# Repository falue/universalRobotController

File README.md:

# Universal Robot Control (RX/TX)

## Introduction

This repository includes transmitter (TX) and receiver (RX) arduino files for a remote controlled robot of any form.

The transmitter is a custom build to have full control over input mixing, skewing and do all sorts of dependencies.
It depends on a custom PCB, or like a thousand wires.
The receiver end can be a robot or whatever.

This relies on OrangeRx products by hobbyking for Tx/Rx and uses the (legacy) DSM2/DSMX† protocols for a reliable, digital communication.
with a "range of up to 3km (line of sight)".
I'm sure though this works with any RC transmitter that uses iBUs / ppm.

> Based on James Brutons RemoteDSM:
> 
> [https://github.com/XRobots/RemoteDSM ↗](https://github.com/XRobots/RemoteDSM)
> 
> [https://youtu.be/5BfRg9CUMYI ↗](https://youtu.be/5BfRg9CUMYI)

† "*The DSM in DSMX stands for Digital Spectrum Modulation and is what creates pure digital control providing an impenetrable radio link immune to all types of interference.*" ([Soruce ↗](https://www.spektrumrc.com/spm-bs-dsmx.html#:~:text=The%20DSM%20in%20DSMX%20stands,to%20all%20types%20of%20interference.))

# Transmission speed
Depending if you need 10 or 20 channels you can choose to use a second transmitter.
The second transmitter leads to more fluctation and/or longer duration of the main `loop()` though. If you need snappy response times, reconsider using a second transmitter.

|Num of Transmitters|Range (ms)|Average (ms)|Median (ms)|
|--|--|--|--|
|1|30-69|31|32|
|2|28-70|45|33|

# Hardware
## TX
- [Arduino Mega ↗](https://store.arduino.cc/products/arduino-mega-2560-rev3)
- One thousand switches and buttons
- One thousand linear potentiometers
- Two three-axis joysticks (ali express article [1↗](https://de.aliexpress.com/item/4001270851701.html) or [2↗](https://de.aliexpress.com/item/1005002965907648.html)) with a pushbutton
- A custom PCB (files here: [gerber.zip](kicad/universalRobotTx/gerber/gerber.zip) | [kicad](kicad/universalRobotTx))
- A laser cut case (files here: [ai](cad/universal_robot_laser.ai) | [dxf](cad/universal_robot_laser.dxf) | [svg](cad/universal_robot_laser.svg))
- One (or two) [OrangeRX DSMX DSM2 transmitter ↗](https://hobbyking.com/en_us/orangerx-dsmx-dsm2-compatible-2-4ghz-transmitter-module-v1-2.html)
- *..extensive list has to follow*

## RX
- [Arduino Leonardo (or UNO) ↗](https://store.arduino.cc/products/arduino-leonardo-with-headers)
- [Arduino Motor Shield Rev3 ↗](https://store.arduino.cc/products/arduino-motor-shield-rev3)
- One  (or two) [OrangeRx RR12RDTS Receiver ↗](https://hobbyking.com/en_us/orangerx-rr12rdts-receiver-with-s-link-dsm2-dsmx-compatible.html)
- [OrangeRx Program box ↗](https://hobbyking.com/en_us/orangerx-program-box-for-r620x-r1220x-v3-rr12rdts-receivers.html)
- *..extensive list has to follow*

---

# OrangeRx setup

## OrangeRx Receiver re-programming
As the Windows software "[rx_secure_configurator ↗](https://cdn-global-hk.hobbyking.com/media/file/r/x/rx_secure_configurator.zip?_gl=1*g1ywqd*_ga*MTM1ODE1NzExLjE3MTE0MDI5MjU.*_ga_5W5MJE4N6Q*MTcxNDIxNzU1Ni4xMS4xLjE3MTQyMTc2MTguNTkuMC4w)" for the [receiver ↗](https://hobbyking.com/en_us/orangerx-rr12rdts-receiver-with-s-link-dsm2-dsmx-compatible.html) to set some settings on the receiver is **very** buggy, buy the [OrangeRx Program box ↗](https://hobbyking.com/en_us/orangerx-program-box-for-r620x-r1220x-v3-rr12rdts-receivers.html).
1. Connect the jumper to power the receiver from the program box to pin 1 and 2.
2. Set the "out type" from default "*SBus*" to "*iBUS*"
3. Set the *FailSafe" to send "1500" on all channels when losing connection; to be able to detect signal loss on the receiver

## OrangeRx Binding Process
1. Power off remote.
2. Power on robot receiver. Its LED flashes fast yellow to indicate that there is no connection.
2. Press "Bind" button on transmitter.
3. Power on remote (!); keep "Bind" button pressed.
4. remote beeps three times; robot receiver stops flashing and has now a continous light. congrats.
5. From here on out, connection is established.

> 📝 NOTE: Red LED on remote (on the transmitter) does not turn on if no signal is sent to the PPM pin.
> 
> 📝 NOTE: Always power on robot receiver first, then remote.
> 
> 📝 NOTE: If turned off remote while robot receiver is on, restart robot receiver as well to reset connection.
> Turning off robot receiver while remote is still on, restarting robot receiver again auto connects again.

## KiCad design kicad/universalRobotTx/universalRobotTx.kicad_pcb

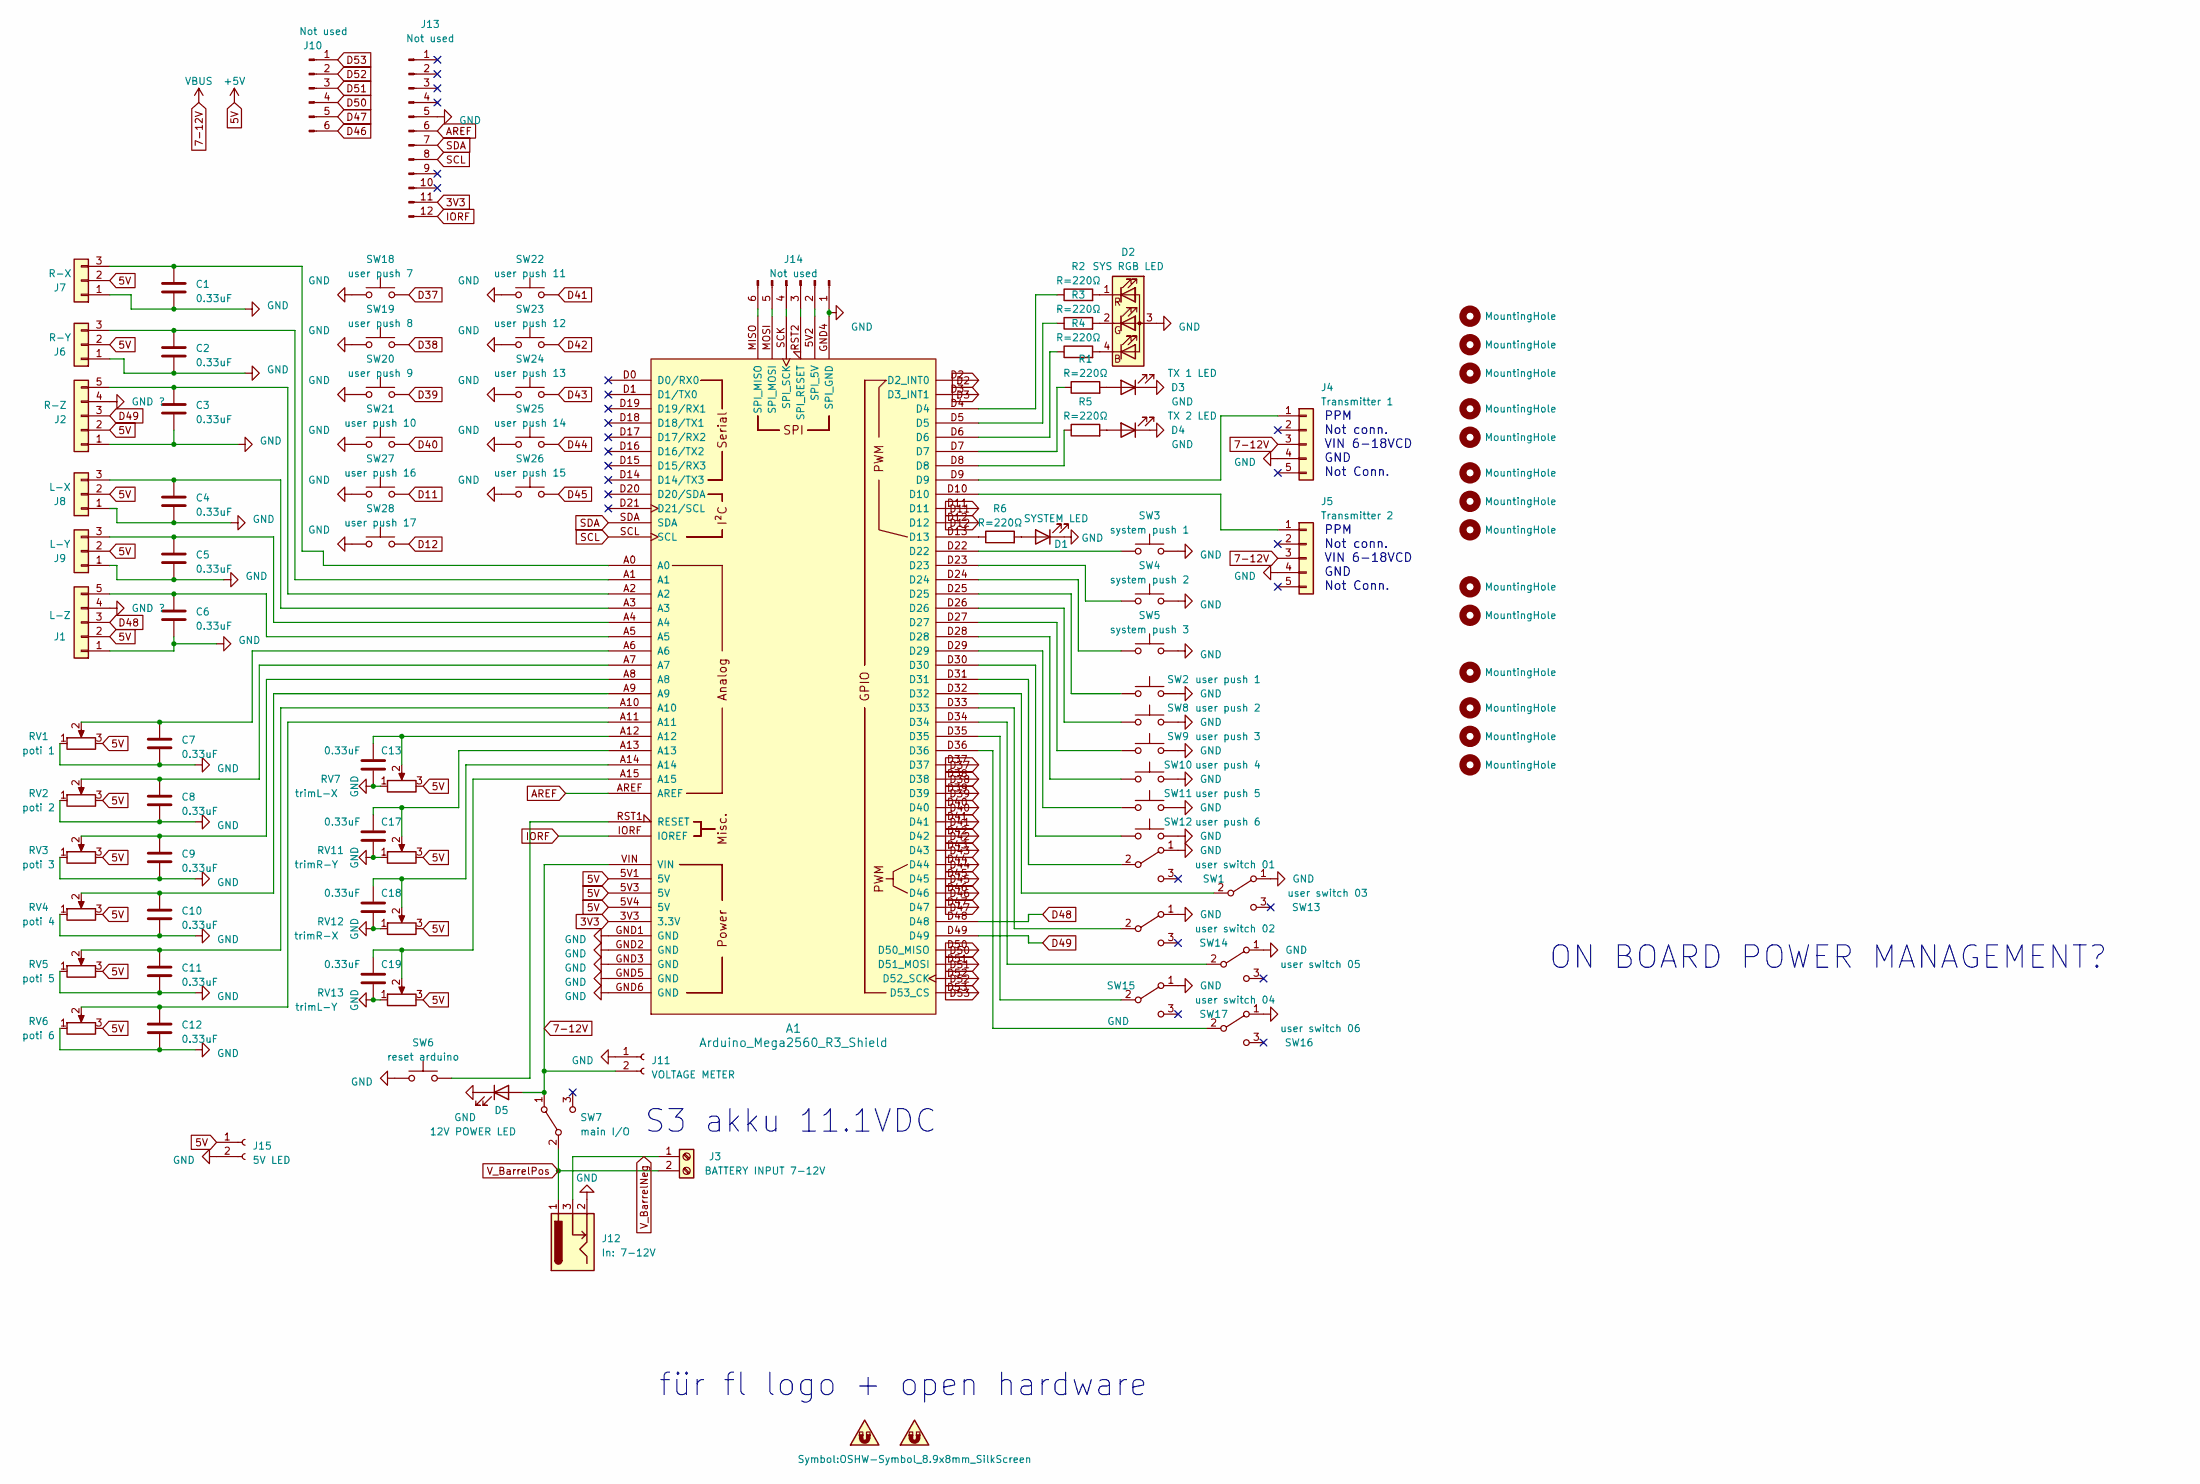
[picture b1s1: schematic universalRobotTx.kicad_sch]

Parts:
A1: Arduino_Mega2560_R3_Shield
C1, C2, C3, C4, C5, C6, C7, C8, C9, C10, C11, C12, C13, C17, C18, C19: 0.33uF; C_Disc_D7.0mm_W2.5mm_P5.00mm
D1: SYSTEM LED; LED_D3.0mm
D2: SYS RGB LED; LED_D5.0mm-4_RGB_Wide_Pins
D3: TX 1 LED; LED_D3.0mm
D4: TX 2 LED; LED_D3.0mm
D5: 12V POWER LED; LED_D3.0mm
H7: MountingHole; MountingHole_3mm
J1: L-Z; JST_PH_B5B-PH-K_1x05_P2.00mm_Vertical
J2: R-Z; JST_PH_B5B-PH-K_1x05_P2.00mm_Vertical
J3: BATTERY INPUT 7-12V; TerminalBlock_Phoenix_MKDS-1,5-2-5.08_1x02_P5.08mm_Horizont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
J4: Transmitter 1; JST_PH_B5B-PH-K_1x05_P2.00mm_Vertical
J5: Transmitter 2; JST_PH_B5B-PH-K_1x05_P2.00mm_Vertical
J6: R-Y; JST_PH_B3B-PH-K_1x03_P2.00mm_Vertical
J7: R-X; JST_PH_B3B-PH-K_1x03_P2.00mm_Vertical
J8: L-X; JST_PH_B3B-PH-K_1x03_P2.00mm_Vertical
J9: L-Y; JST_PH_B3B-PH-K_1x03_P2.00mm_Vertical
J10, J14: Not used; PinHeader_1x06_P2.54mm_Vertical
J11: VOLTAGE METER; JST_EH_B2B-EH-A_1x02_P2.50mm_Vertical
J12: In: 7-12V; BarrelJack_Kycon_KLDX-0202-xC_Horizontal
J13: Not used; PinHeader_1x12_P2.54mm_Vertical
J15: 5V LED; JST_EH_B2B-EH-A_1x02_P2.50mm_Vertical
R1, R2, R3, R4, R5, R6: R=220Ω; R_Axial_DIN0309_L9.0mm_D3.2mm_P5.08mm_Vertical
RV1: poti 1; Potentiometer_Bourns_PTV09A-1_Single_Vertical
RV2: poti 2; Potentiometer_Bourns_PTV09A-1_Single_Vertical
RV3: poti 3; Potentiometer_Bourns_PTV09A-1_Single_Vertical
RV4: poti 4; Potentiometer_Bourns_PTV09A-1_Single_Vertical
RV5: poti 5; Potentiometer_Bourns_PTV09A-1_Single_Vertical
RV6: poti 6; Potentiometer_Bourns_PTV09A-1_Single_Vertical
RV7: trimL-X; Potentiometer_Bourns_3386X_Horizontal
RV11: trimR-Y; Potentiometer_Bourns_3386X_Horizontal
RV12: trimR-X; Potentiometer_Bourns_3386X_Horizontal
RV13: trimL-Y; Potentiometer_Bourns_3386X_Horizontal
SW1: user switch 01; Toggle_switch_3P_5.08
SW2: user push 1; SW_TH_Tactile_FL_thingy
SW3: system push 1; Drucktaster_FL_Mentor_1852.6231
SW4: system push 2; Drucktaster_FL_Mentor_1852.6231
SW5: system push 3; Drucktaster_FL_Mentor_1852.6231
SW6: reset arduino; Drucktaster_FL_Mentor_1852.6231
SW7: main I/O; Toggle_switch_3P_5.08
SW8: user push 2; SW_TH_Tactile_FL_thingy
SW9: user push 3; SW_TH_Tactile_FL_thingy
SW10: user push 4; SW_TH_Tactile_FL_thingy
SW11: user push 5; SW_TH_Tactile_FL_thingy
SW12: user push 6; SW_TH_Tactile_FL_thingy
SW13: user switch 03; Toggle_switch_3P_5.08
SW14: user switch 02; Toggle_switch_3P_5.08
SW15: user switch 05; Toggle_switch_3P_5.08
SW16: user switch 06; Toggle_switch_3P_5.08
SW17: user switch 04; Toggle_switch_3P_5.08
SW18: user push 7; SW_Push_1P2T_Horizontal_FL_RND_210-00255
SW19: user push 8; SW_Push_1P2T_Horizontal_FL_RND_210-00255
SW20: user push 9; SW_Push_1P2T_Horizontal_FL_RND_210-00255
SW21: user push 10; SW_Push_1P2T_Horizontal_FL_RND_210-00255
SW22: user push 11; SW_Push_1P2T_Horizontal_FL_RND_210-00255
SW23: user push 12; SW_Push_1P2T_Horizontal_FL_RND_210-00255
SW24: user push 13; SW_Push_1P2T_Horizontal_FL_RND_210-00255
SW25: user push 14; SW_Push_1P2T_Horizontal_FL_RND_210-00255
SW26: user push 15; SW_Push_1P2T_Horizontal_FL_RND_210-00255
SW27: user push 16; SW_Push_1P2T_Horizontal_FL_RND_210-00255
SW28: user push 17; SW_Push_1P2T_Horizontal_FL_RND_210-00255

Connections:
3V3: A1.3V3 (3.3V), J13.11
5V: A1.5V1 (5V), A1.5V3 (5V), A1.5V4 (5V), J1.2, J2.2, J6.2, J7.2, J8.2, J9.2, J15.1, RV1.3, RV2.3, RV3.3, RV4.3, RV5.3, RV6.3, RV7.3, RV11.3, RV12.3, RV13.3
7-12V: A1.VIN, D5.2 (A), J4.3, J5.3, J11.2, SW7.1 (A)
AREF: A1.AREF, J13.6
D2: A1.D2 (D2_INT0)
D3: A1.D3 (D3_INT1)
D11: A1.D11, SW27.2
D12: A1.D12, SW28.2
D37: A1.D37, SW18.2
D38: A1.D38, SW19.2
D39: A1.D39, SW20.2
D40: A1.D40, SW21.2
D41: A1.D41, SW22.2
D42: A1.D42, SW23.2
D43: A1.D43, SW24.2
D44: A1.D44, SW25.2
D45: A1.D45, SW26.2
D46: A1.D46, J10.6
D47: A1.D47, J10.5
D48: A1.D48, J1.3
D49: A1.D49, J2.3
D50: A1.D50 (D50_MISO), J10.4
D51: A1.D51 (D51_MOSI), J10.3
D52: A1.D52 (D52_SCK), J10.2
D53: A1.D53 (D53_CS), J10.1
IORF: A1.IORF (IOREF), J13.12
unnamed: A1.A6, C7.1, RV1.2
unnamed: A1.A7, C8.1, RV2.2
unnamed: A1.A8, C9.1, RV3.2
unnamed: A1.A9, C10.1, RV4.2
unnamed: A1.A10, C11.1, RV5.2
unnamed: A1.A11, C12.1, RV6.2
unnamed: A1.A12, C13.1, RV7.2
unnamed: A1.A13, C17.1, RV11.2
unnamed: A1.A14, C18.1, RV12.2
unnamed: A1.A15, C19.1, RV13.2
unnamed: A1.D4, R2.1
unnamed: A1.D5, R3.1
unnamed: A1.D6, R4.1
unnamed: A1.D7, R1.1
unnamed: A1.D8, R5.1
unnamed: A1.D13, R6.1
unnamed: A1.D22, SW3.1
unnamed: A1.D23, SW4.1
unnamed: A1.D24, SW5.1
unnamed: A1.D25, SW2.1
unnamed: A1.D26, SW8.1
unnamed: A1.D27, SW9.1
unnamed: A1.D28, SW10.1
unnamed: A1.D29, SW11.1
unnamed: A1.D30, SW12.1
unnamed: A1.RST1 (RESET), SW6.2
unnamed: A1.5V2 (SPI_5V), J14.2
unnamed: A1.MISO (SPI_MISO), J14.6
unnamed: A1.MOSI (SPI_MOSI), J14.5
unnamed: A1.RST2 (SPI_RESET), J14.3
unnamed: A1.SCK (SPI_SCK), J14.4
unnamed: D1.2 (A), R6.2
unnamed: D2.4 (BK), R4.2
unnamed: D2.2 (GK), R3.2
unnamed: D2.1 (RK), R2.2
unnamed: D3.2 (A), R1.2
unnamed: D4.2 (A), R5.2
unnamed: A1.A5, C6.1, J1.5
unnamed: A1.A2, C3.1, J2.5
unnamed: A1.D9, J4.1
unnamed: A1.D10, J5.1
unnamed: A1.A1, C2.1, J6.3
unnamed: A1.A0, C1.1, J7.3
unnamed: A1.A3, C4.1, J8.3
unnamed: A1.A4, C5.1, J9.3
unnamed: A1.D31, SW1.2 (B)
unnamed: A1.D32, SW13.2 (B)
unnamed: A1.D33, SW14.2 (B)
unnamed: A1.D34, SW15.2 (B)
unnamed: A1.D36, SW16.2 (B)
unnamed: A1.D35, SW17.2 (B)
SCL: A1.SCL, J13.8
SDA: A1.SDA, J13.7
V_BarrelNeg: J3.1, J12.3
V_BarrelPos: J3.2, J12.1, SW7.2 (B)

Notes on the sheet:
PPM Not conn. VIN 6-18VCD GND Not Conn.
ON BOARD POWER MANAGEMENT?
S3 akku 11.1VDC
für fl logo + open hardware

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
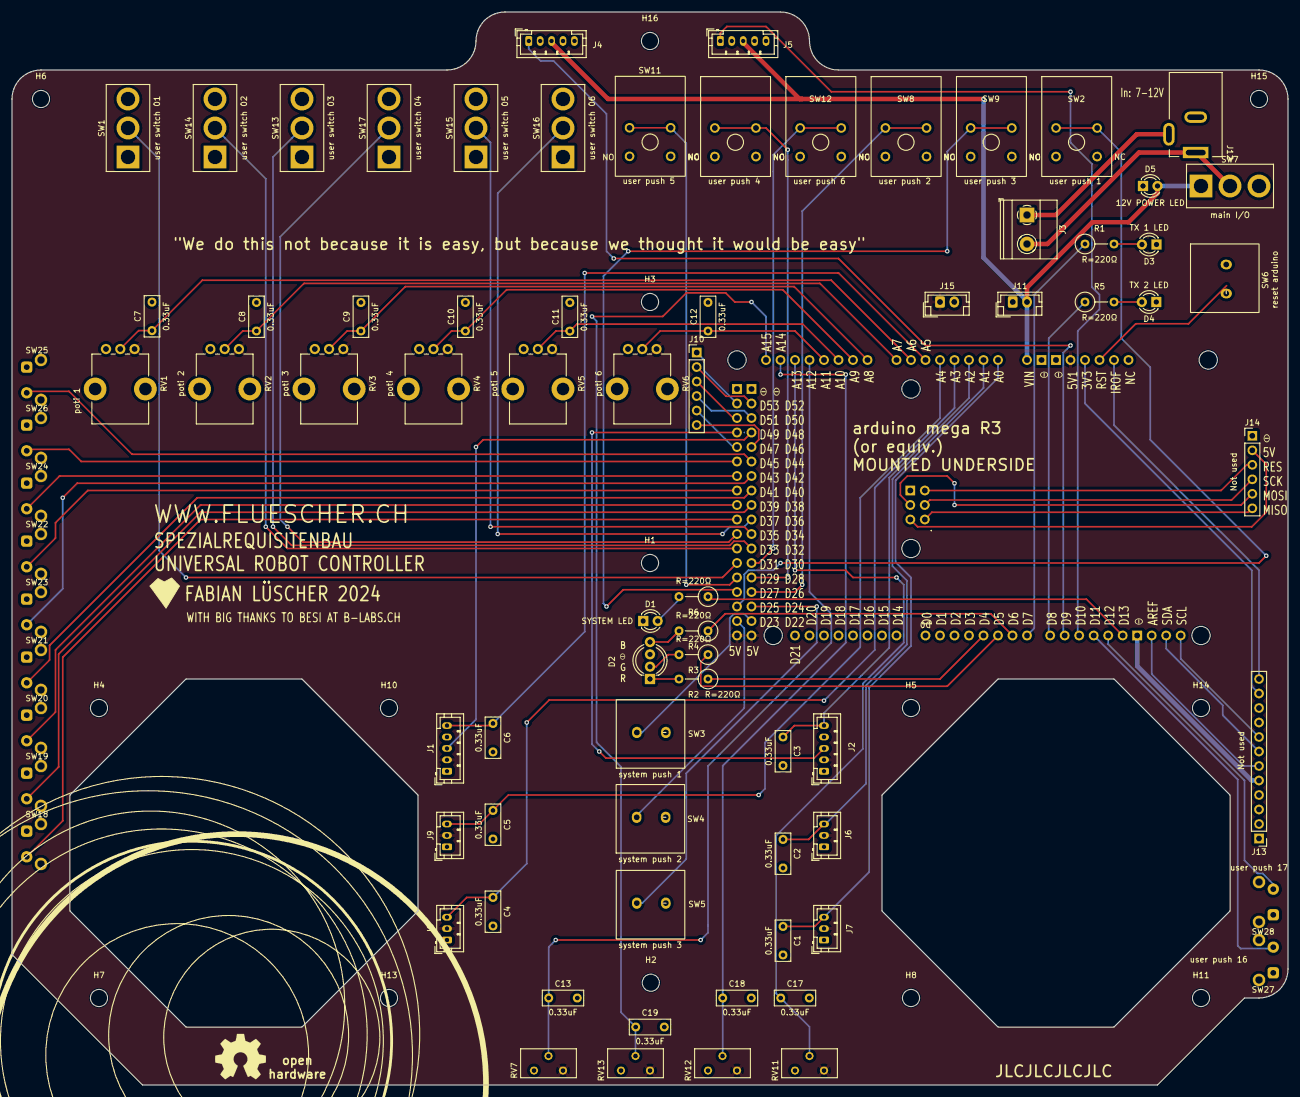
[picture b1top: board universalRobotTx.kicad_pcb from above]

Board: 2 copper layers, 223.5 x 188.0 mm, 95 parts (0 on the bottom side), 80 nets.

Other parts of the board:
H1, H2, H3, H4, H5, H6, H8, H10, H11, H13, H14, H15, H16: MountingHole; MountingHole_3mm

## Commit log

2024-04-10 ignore _archive folder
2024-04-10 first approach of sending data
2024-04-10 add more CAD options
2024-04-12 Connect 5V to the the Label, Label the 7-12V to VBUS, Connect SPI GND to GNDs Add Barrel Power Label for Netclass
2024-04-12 Update tolerances
2024-04-12 Redo the routing
2024-04-12 Use wide pins for RGB LED
2024-04-12 Add encode functions
2024-04-12 New footprints, edit footprints, turn stuff around
2024-04-12 Move design elements
2024-04-12 Move one edge
2024-04-12 backups kicad
2024-04-12 remove some backups somehow
2024-04-12 minor changes
2024-04-12 Add gerber files
2024-04-12 some further minor changes
2024-04-12 Some minor details added; new gerber export for production
2024-04-13 Add drill (.drl) files to gerber export for JLC order
2024-04-19 Kicad auto Backups
2024-04-27 Add kicad backups
2024-04-27 Add note about binding receiver
2024-04-27 Add details
2024-04-27 Remove terrible version
2024-04-27 First working version
2024-04-27 Buttons are now value-shifted, varia
2024-04-27 Add testing scripts for steering and processing 4 sketch for visuals
2024-04-27 Add infos about Receiver re-programming
2024-04-27 Shorten PPM gap inbetween signals, somehow works
2024-04-27 Semantically renaming of renaming channels
2024-04-29 Add missing pde file
2024-04-29 Add failsafe hint
2024-04-29 Cleanup & sysBtn1 halts program
2024-05-06 Add test for ruleOfThree function
2024-05-06 Add play field for head movement calibration$
2024-05-06 Add vscode worskpace folder
2024-05-06 Change port
2024-05-06 Cleanup
2024-05-06 Do not use interrupts for reading signal
2024-05-06 Attach/detach servos when needed
2024-05-07 Oopsie mororR received the same value as motorL
2024-05-08 Reorganize helper and text scripts
2024-05-08 Fit visuals to the new dogma
2024-05-08 Encode 4 switches and buttons for 1 channel
2024-05-08 Decode 4 buttons on one channel
2024-05-08 Swap pins around
2024-05-08 Better comments
2024-05-08 Speed is changed by poti1
2024-05-08 Better annotate helper scripts
2024-05-09 click and drag joystick when no serial available
2024-05-09 Make internal calculateMotorSpeed work without using USB serial
2024-05-09 Make calculateMotorSpeed work
2024-05-09 Finalize motor controls for driving
2024-05-09 Quickturn by joy btn presses
2024-05-09 Increase death zone
2024-05-09 Head movement smoothing finalized; accelerated smoothing by sw3
2024-05-09 Quickest turn 1°; debounce btn on demand
2024-05-09 Disable quickturn if enableDrive is false
2024-05-09 Disable steering switch
2024-05-09 Fine tune smoothing head servos
2024-05-09 Add some basic infos
2024-05-09 Add infos about DSMX and so on
2024-05-10 Prepare usage for second transmitter
2024-05-10 Trim main joystick axis' as variable - range 255 instead of 1024
2024-05-10 Comment about which channel will be which btns, naming convention
2024-05-10 Add loop() speed information
2024-05-20 Match servo value to physical servo arm
2024-05-20 First sketch for curves generator
2024-05-20 Add explanation for curves script3
2025-09-30 Add foam insert drawing
2025-09-30 update kicad files
2025-09-30 Make easier to select which btns/pots are sent over which channel
2025-10-01 Ignore chn3
2025-10-01 Constrain trimmed pots to valid values 1000-2000
2025-10-01 Debug prints for trim pots
2025-10-01 Bugfixes for iBUS signal generation
